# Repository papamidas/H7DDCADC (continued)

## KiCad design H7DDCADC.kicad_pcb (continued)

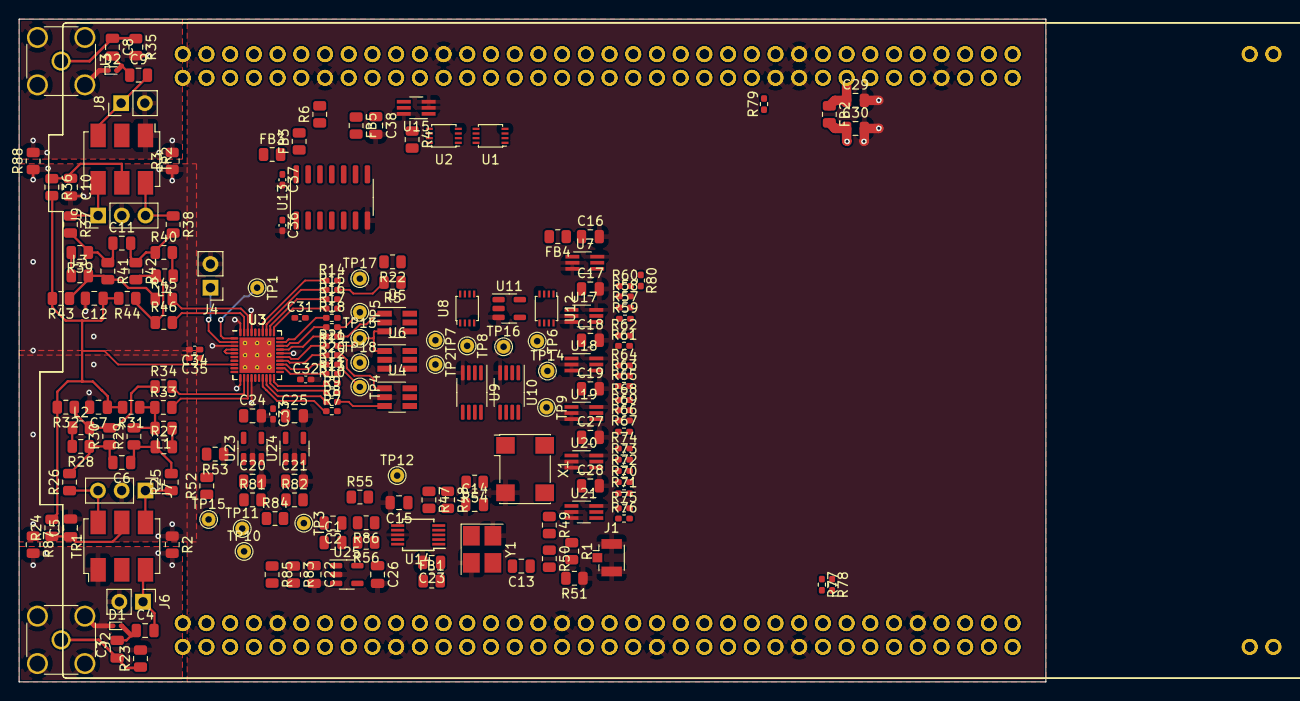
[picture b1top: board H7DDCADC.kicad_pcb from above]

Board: 4 copper layers, 110.0 x 71.0 mm, 194 parts (0 on the bottom side), 145 nets.

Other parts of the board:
C8, C9, C10, C12: 100n; C_0805_2012Metric
C11: 100pF; C_0805_2012Metric
D2: ESD9B3.3ST5G; D_SOD-923
FB3#2, FB4: Ferrite_0805; R_0805_2012Metric
J8: HDR2; PinHeader_1x02_P2.54mm_Vertical
J9: HDR3; PinHeader_1x03_P2.54mm_Vertical
L3, L4: 180nH; R_0805_2012Metric
R35: 1M; R_0805_2012Metric
R36, R37, R38, R39, R40: 0R; R_0805_2012Metric
R41, R42: 33R; R_0805_2012Metric
R43, R44: 24.9R; R_0805_2012Metric
R45, R46: 10R; R_0805_2012Metric
TR2: ADT1-6T; Mini-Circuits_CD637_H5.23mm
U3#2: ADC3660IRSBT; QFN-40-1EP_5x5mm_P0.4mm_EP3.6x3.6mm
U16#2: NUCLEO144-H743ZI; ST_Morpho_Connector_144_STLink

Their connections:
+3.3VF: FB3#2.2, FB4.2; also elsewhere on the board
+3V3: U16#2.16 (+3V3); also elsewhere on the board
/ADC/AIN_N: U3#2.13 (AINM); also elsewhere on the board
/ADC/AIN_P: U3#2.12 (AINP); also elsewhere on the board
/ADC/BIN_N: R45.2, U3#2.38 (BINM); also elsewhere on the board
/ADC/BIN_P: R46.2, U3#2.39 (BINP); also elsewhere on the board
/ADC/CLKN_ADC: U3#2.7 (CLKM); also elsewhere on the board
/ADC/CLKP_ADC: U3#2.6 (CLKP); also elsewhere on the board
/ADC/PDN_SYNC: U3#2.1 (PDN/SYNC); also elsewhere on the board
/ADC/RESET: U3#2.9 (RESET); also elsewhere on the board
/ADC/SCLK: U3#2.35 (SCLK); also elsewhere on the board
/ADC/SDIO: U3#2.10 (SDIO); also elsewhere on the board
/ADC/SEN: U3#2.16 (/SEN); also elsewhere on the board
/ADC/VREF: U3#2.2 (VREF); also elsewhere on the board
/GNDI_B: D2.1 (A1), J8.2, R35.2, TR2.1; also elsewhere on the board
/IN_B_50: C8.1, R35.1; also elsewhere on the board
/MCU/+5V: U16#2.18 (+5V); also elsewhere on the board
/MCU/E5V: U16#2.6 (E5V); also elsewhere on the board
/MCU/I2C1_SCL_A: U16#2.89 (PB6); also elsewhere on the board
/MCU/I2C1_SCL_B: U16#2.75 (PB8); also elsewhere on the board
/MCU/I2C1_SDA_A: U16#2.21 (LD2/PB7); also elsewhere on the board
/MCU/PE1: U16#2.61 (PE1); also elsewhere on the board
/MCU/PF0_50: U16#2.53 (PF0); also elsewhere on the board
/MCU/SPI2_MOSI_A: U16#2.36 (ETH_MDC/PC1); also elsewhere on the board
/MCU/SPI2_MOSI_B: U16#2.37 (PC3); also elsewhere on the board
/MCU/SPI2_MOSI_C: U16#2.98 (PB15); also elsewhere on the board
/MCU/SPI2_NSS_A: U16#2.88 (PB12); also elsewhere on the board
/MCU/SPI2_NSS_B: U16#2.86 (USB_DM/PA11); also elsewhere on the board
/MCU/SPI2_NSS_C: U16#2.99 (PB4); also elsewhere on the board
/MCU/SPI2_NSS_D: U16#2.77 (PB9); also elsewhere on the board
/MCU/SPI2_SCK_A: U16#2.97 (PB10); also elsewhere on the board
/MCU/SPI2_SCK_B: U16#2.102 (ETH_TXD1/PB13); also elsewhere on the board
/MCU/SPI2_SCK_C: U16#2.93 (USB_VBUS/PA9); also elsewhere on the board
/MCU/SPI2_SCK_D: U16#2.84 (USB_DP/PA12); also elsewhere on the board
/MCU/SPI2_SCK_E: U16#2.40 (PD3); also elsewhere on the board
/MCU/SPI3_MOSI_A: U16#2.94 (PB2); also elsewhere on the board
/MCU/SPI3_MOSI_B: U16#2.101 (PB5); also elsewhere on the board
/MCU/SPI3_MOSI_C: U16#2.43 (PD6); also elsewhere on the board
/MCU/SPI3_MOSI_D: U16#2.3 (PC12); also elsewhere on the board
/MCU/SPI3_NSS_A: U16#2.17 (PA15); also elsewhere on the board
/MCU/SPI3_NSS_B: U16#2.32 (PA4); also elsewhere on the board
/MCU/SPI3_SCK_A: U16#2.1 (PC10); also elsewhere on the board
/MCU/SPI3_SCK_B: U16#2.103 (SWO/PB3); also elsewhere on the board
/MCU/SPI4_MISO: U16#2.50 (PE5); also elsewhere on the board
/MCU/SPI4_MOSI: U16#2.62 (PE6); also elsewhere on the board
/MCU/SPI4_NSS: U16#2.48 (PE4); also elsewhere on the board
/MCU/SPI4_SCK: U16#2.46 (PE2); also elsewhere on the board
/MCU/U5V: U16#2.80 (U5V); also elsewhere on the board
/MCU/VDD: U16#2.5 (VDD); also elsewhere on the board
/MCU/VIN: U16#2.24 (VIN); also elsewhere on the board
AVDD: U3#2.4 (REFBUF), U3#2.5 (AVDD), U3#2.15 (AVDD), U3#2.36 (AVDD); also elsewhere on the board
GND: C10.2, C12.2, J9.2, U3#2.3 (REFGND), U3#2.11 (GND), U3#2.14 (GND), U3#2.26 (IOGND), U3#2.37 (GND), U3#2.40 (GND), U3#2.41 (GND_PAD), U16#2.8 (GND), U16#2.19 (GND), U16#2.20 (GND), U16#2.22 (GND), U16#2.49 (GND), U16#2.60 (GND), U16#2.71 (GND), U16#2.72 (GND), U16#2.81 (GND), U16#2.92 (GND), U16#2.104 (AGND), U16#2.111 (GND), U16#2.126 (GND), U16#2.135 (GND), U16#2.143 (GND), U16#2.144 (GND); also elsewhere on the board
IOVDD: U3#2.21 (IOVDD), U3#2.30 (IOVDD); also elsewhere on the board
unnamed: C8.2, C9.1, D2.2 (A2)
unnamed: C9.2, J8.1, TR2.3
unnamed: C10.1, R36.1, TR2.5
unnamed: C11.1, R37.2, R39.1, R41.1
unnamed: C11.2, R38.2, R40.1, R42.1
unnamed: J9.1, R37.1, TR2.4
unnamed: J9.3, R38.1, TR2.6
unnamed: L3.1, R39.2
unnamed: L3.2, R41.2, R43.1, R45.1
unnamed: L4.1, R40.2
unnamed: L4.2, R42.2, R44.1, R46.1
unnamed 107: U3#2.17 (NC); also elsewhere on the board
unnamed 108: U3#2.18 (FCLK); also elsewhere on the board
unnamed 109: U3#2.19 (NC); also elsewhere on the board
unnamed 110: U3#2.20 (NC); also elsewhere on the board
unnamed 111: U3#2.22 (NC); also elsewhere on the board
unnamed 112: U3#2.23 (DA5); also elsewhere on the board
unnamed 113: U3#2.24 (DA6); also elsewhere on the board
unnamed 114: U3#2.34 (NC); also elsewhere on the board
unnamed 115: U3#2.33 (DCLKIN); also elsewhere on the board
unnamed 116: U3#2.32 (NC); also elsewhere on the board
unnamed 117: U3#2.31 (NC); also elsewhere on the board
unnamed 118: U3#2.29 (NC); also elsewhere on the board
unnamed 119: U3#2.28 (DB5); also elsewhere on the board
unnamed 120: U3#2.27 (DB6); also elsewhere on the board
unnamed 121: U3#2.25 (DCLK); also elsewhere on the board
V1T97: FB4.1; also elsewhere on the board
VCM: C12.1, R36.2, R43.2, R44.2, U3#2.8 (VCM); also elsewhere on the board

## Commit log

2022-07-10 annotated and packages defined
2022-07-17 placement_in_progress 1
2022-07-22 placement 80 percent
2022-07-26 routing in progress 1
2022-07-27 routing in progress 2
2022-07-27 routing done
2022-07-28 Silkscreen edited
2022-07-29 JLCPCB order
